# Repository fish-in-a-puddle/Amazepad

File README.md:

# Amazepad

A hackpad with six keys, a rotary encoder and a small OLED display featuring Rocky from Project Hail Mary to help you with your projects.

#### This project was made for Hack Club's Stardance! Check it out [here](https://stardance.hackclub.com/projects/46887)

#### If you're a teenager wanting to make your own hackpad, you can find the tutorial [here](https://hackpad.hackclub.com/)

## Inspiration

A few weeks ago, I saw an interesting project on Reddit - a small voice assistant on a Raspberry Pi that talked like Rocky from Project Hail Mary. I had also been looking at the hackpads submitted through Stardance, so I thought "What about a hackpad with an engineering friend to encourage you?". This Rocky doesn't respond to questions, of course, but he shows different messages on the OLED depending on how fast you're typing.

## Layout

The Amazepad features 6 mechanical keyswitches and one rotary encoder. In my firmware, the rotary encoder controls the computer's volume and the keys are arranged like so:

| MUTE | CRTL+A | CTRL+Z |

| CTRL+C | CTRL+V | CTRL+S |

The Amazepad also has a 0.91" OLED display that shows three different images depending on your WPM, all pixel art of Rocky with one of his favorite phrases.

## Design

Before starting this project, I had never made a PCB before. It took a little while to get used to Kicad, but I eventually got everything properly connected. I had originally planned to add a second rotary encoder and lights under each key, but that ended up being way more complicated than I was prepared for, so I scaled back the design to make it easier to solder and program. Once the PCB was done, I moved on to designing the case.

The tutorial suggested using Fusion 360, so I downloaded it. The moment I opened it, I regretted it. Nothing worked - not even drawing a rectangle. I probably could have hunkered down, watched some videos and figured it out in a few hours, but I didn't. I went back to the ever-reliable Sketchup and made a simple case there. Just a rectangle box with cutouts on the cover. I plan to add some stickers to it once I print it to make it a little cooler, though.

As for the firmware, I used QMK to port the macropad and set everything up. That took a while and a whole lot of trial and error. At this point the firmware has not been tested (as I do not have the actual hackpad yet) but I am fairly confident that it will work.

## Bill of Materials

|Part                 |Qty|Cost(USD)|Source        |
|---------------------|---|---------|--------------|
|4.7k ohm resistor    | 2 | $0      | My workspace |
|1N4148 diode         | 6 | $0      | Hackpad kit  |
|Cherry MX keyswitches| 6 | $0      | Hackpad kit  |
|Rotary encoder       | 1 | $0      | Hackpad kit  |
|Seeeduino Xiao RP2040| 1 | $0      | Hackpad kit  |
|0.91 OLED            | 1 | $0      | Hackpad kit  |

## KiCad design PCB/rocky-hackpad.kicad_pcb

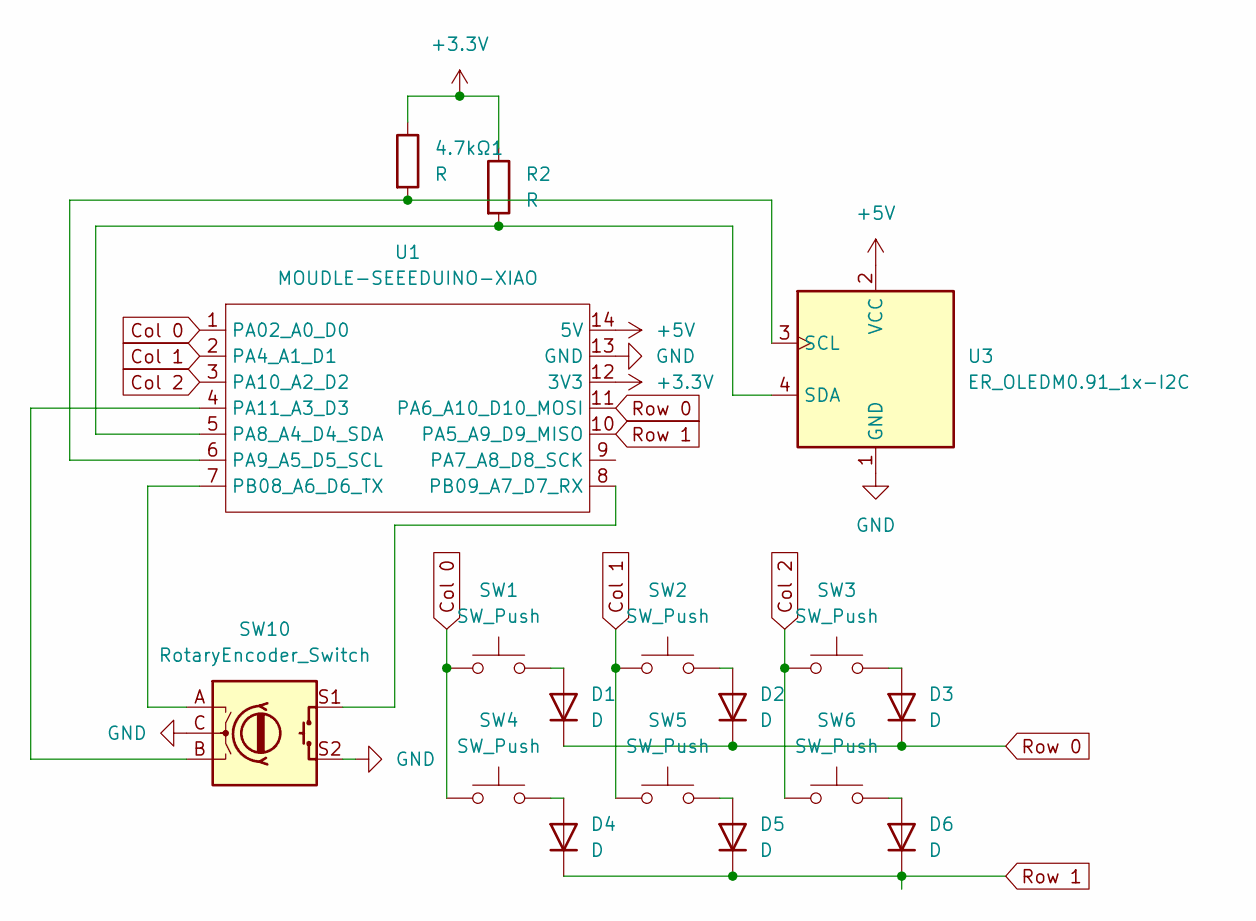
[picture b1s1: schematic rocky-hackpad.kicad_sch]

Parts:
4.7kΩ1: R; R_0201_0603Metric
D1, D2, D3, D4, D5, D6: D; D_DO-35_SOD27_P7.62mm_Horizontal
R2: R; R_0201_0603Metric
SW1, SW2, SW3, SW4, SW5, SW6: SW_Push; SW_Cherry_MX_1.00u_PCB
SW10: RotaryEncoder_Switch; RotaryEncoder_Alps_EC11E-Switch_Vertical_H20mm
U1: MOUDLE-SEEEDUINO-XIAO; XIAO-Generic-Hybrid-14P-2.54-21X17.8MM
U3: ER_OLEDM0.91_1x-I2C

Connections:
+3.3V: 4.7kΩ1.1, R2.1, U1.12 (3V3)
+5V: U1.14 (5V), U3.2 (VCC)
Col 0: SW1.1, SW4.1, U1.1 (PA02_A0_D0)
Col 1: SW2.1, SW5.1, U1.2 (PA4_A1_D1)
Col 2: SW3.1, SW6.1, U1.3 (PA10_A2_D2)
GND: SW10.C, SW10.S2, U1.13 (GND), U3.1 (GND)
unnamed: D1.2 (A), SW1.2
unnamed: D2.2 (A), SW2.2
unnamed: D3.2 (A), SW3.2
unnamed: D4.2 (A), SW4.2
unnamed: D5.2 (A), SW5.2
unnamed: D6.2 (A), SW6.2
unnamed: R2.2, U1.5 (PA8_A4_D4_SDA), U3.4 (SDA)
unnamed: 4.7kΩ1.2, U1.6 (PA9_A5_D5_SCL), U3.3 (SCL)
unnamed: SW10.B, U1.4 (PA11_A3_D3)
unnamed: SW10.A, U1.7 (PB08_A6_D6_TX)
unnamed: SW10.S1, U1.8 (PB09_A7_D7_RX)
Row 0: D1.1 (K), D2.1 (K), D3.1 (K), U1.11 (PA6_A10_D10_MOSI)
Row 1: D4.1 (K), D5.1 (K), D6.1 (K), U1.10 (PA5_A9_D9_MISO)

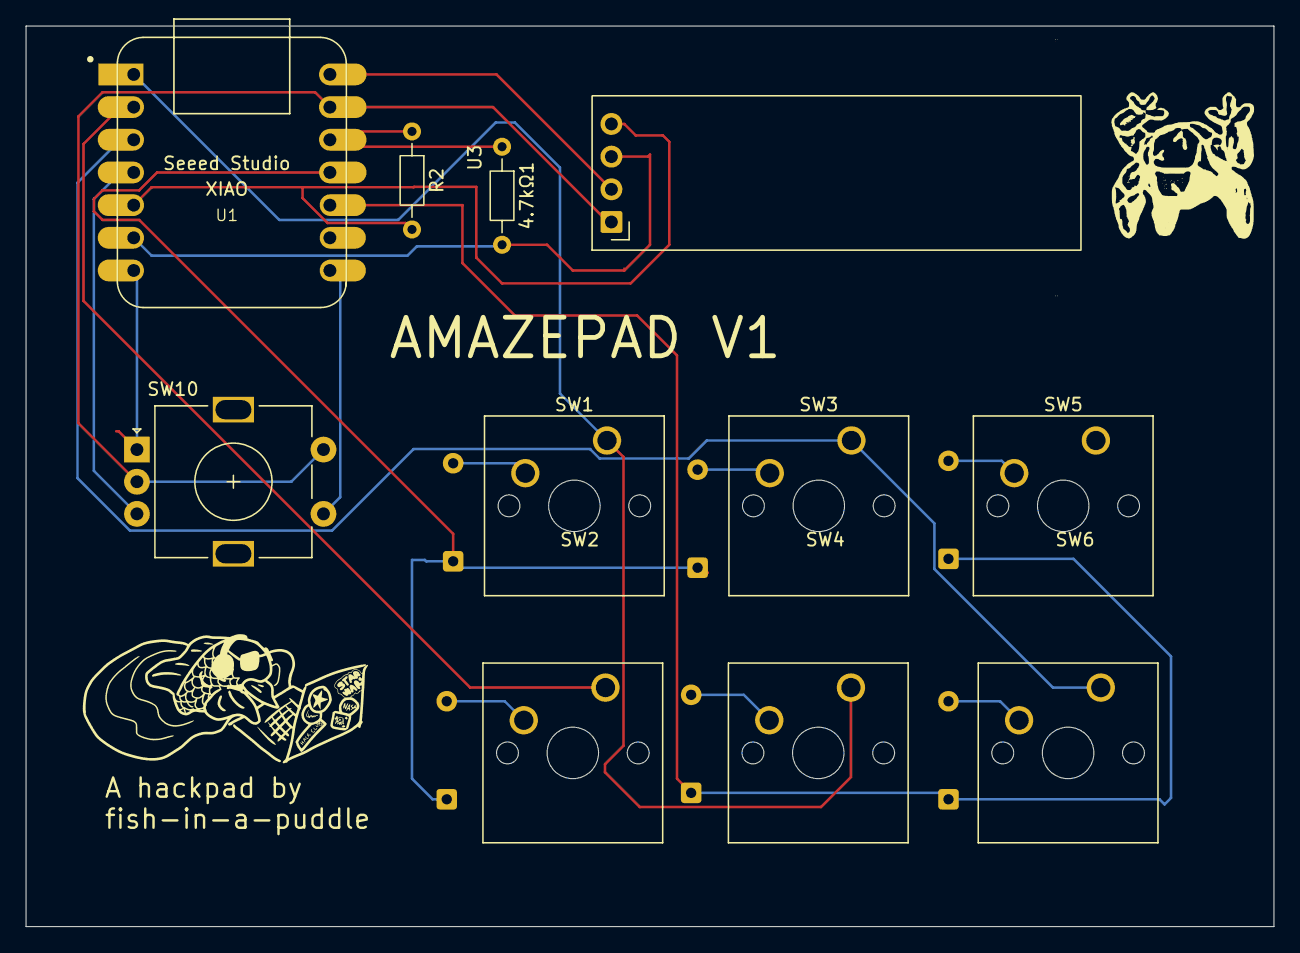
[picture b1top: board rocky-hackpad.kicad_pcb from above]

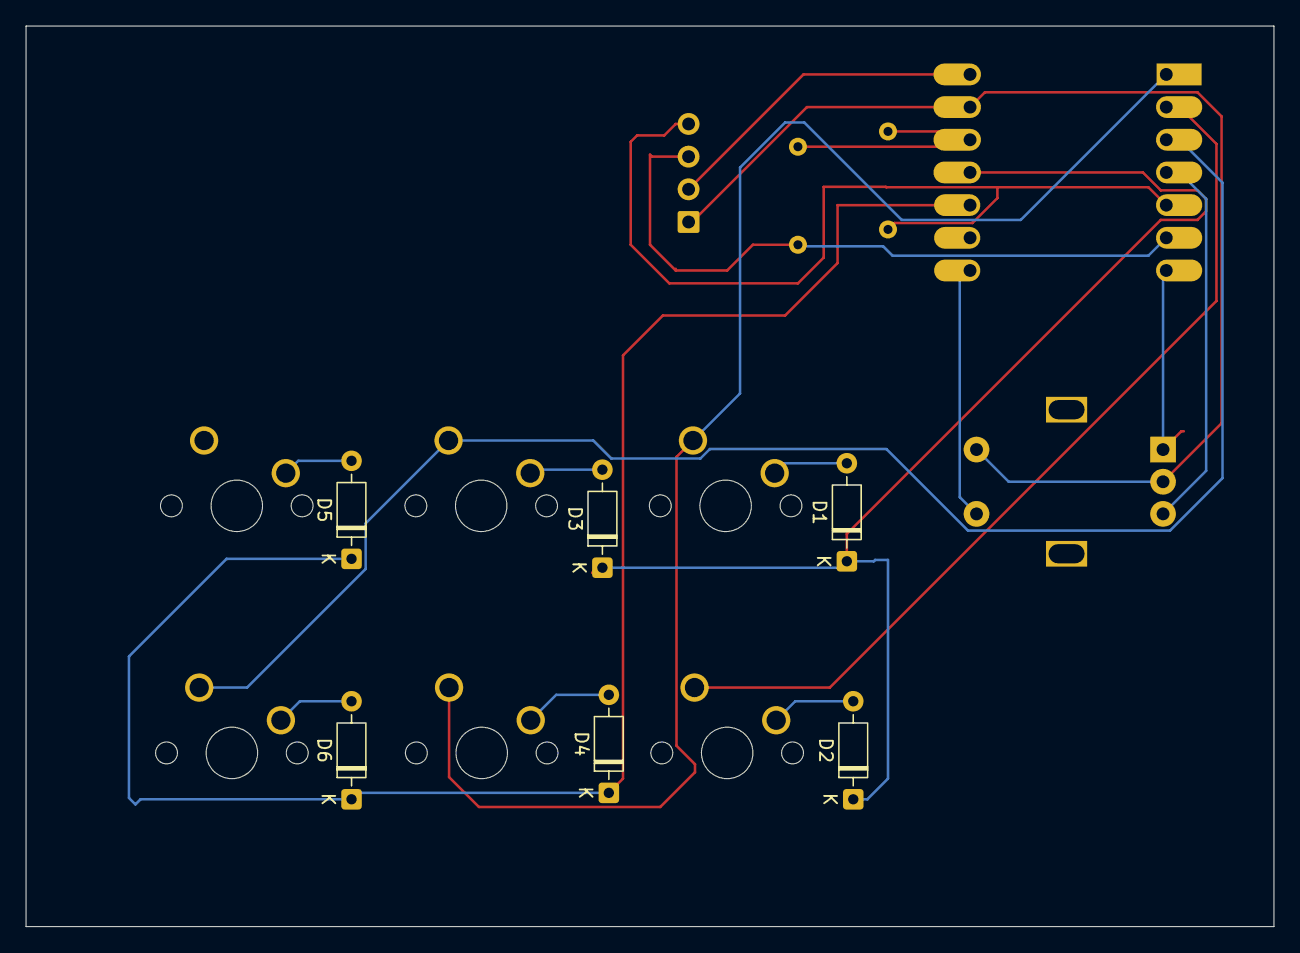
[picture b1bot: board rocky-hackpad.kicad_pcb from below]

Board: 2 copper layers, 97.0 x 70.0 mm, 17 parts (6 on the bottom side), 19 nets.
